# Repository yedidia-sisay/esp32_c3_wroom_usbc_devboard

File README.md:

# ESP32-C3 Custom Development Board

A custom ESP32-C3 development board designed from the ground up in **KiCad**, covering schematic design, component selection, PCB layout, and routing.

The board is built around the **ESP32-C3-WROOM-02** and provides USB-C connectivity, regulated 3.3 V power, programming/debugging interfaces, GPIO expansion, and basic user controls.

## Overview

The goal of this project was to design a practical, compact ESP32-C3 development board rather than relying on an off-the-shelf development board.

The design integrates the ESP32-C3 module with the supporting power, USB, reset, boot, programming, and expansion circuitry required for a usable development platform.

## Features

* **ESP32-C3-WROOM-02** module
* **USB-C** connector
* USB 2.0 D+ / D− connectivity
* USB-C CC resistors
* USB ESD/TVS protection
* **5 V USB input**
* **3.3 V regulated supply**
* AP2112K-3.3 LDO
* Reset / CHIP_PU circuitry
* Boot-mode control
* User/status LED
* GPIO expansion headers
* Dedicated JTAG/UART access
* Exposed 3.3 V, 5 V, and GND connections
* Custom PCB layout and routing

## Hardware

### Main MCU

The board uses the **Espressif ESP32-C3-WROOM-02** module.

The module provides the main processing, USB connectivity, GPIO, UART, and debugging interfaces for the board.

The schematic exposes the ESP32-C3 GPIOs through headers so the board can be used for firmware development and hardware experimentation.

### USB-C

USB-C is used as the primary connection to the board.

The USB interface includes:

* VBUS power input
* USB D+
* USB D−
* CC1 / CC2 configuration resistors
* USB ESD/TVS protection
* Shield connection

The USB data lines connect directly to the ESP32-C3's native USB interface.

### Power

The board accepts **5 V from USB-C**.

A dedicated **AP2112K-3.3 LDO** generates the 3.3 V rail used by the ESP32-C3 and associated circuitry.
Decoupling capacitors are included around the power circuitry and ESP32-C3 supply.

### Reset and Boot

The board includes dedicated push buttons and supporting resistors for:

* ESP32 reset / CHIP_PU
* Boot-mode selection

This allows the module to be manually reset and placed into the required boot mode during firmware development.

### Programming and Debugging

The design exposes the ESP32-C3's programming/debugging signals through dedicated headers.

Interfaces available on the board include:

* UART
* JTAG
* GPIO
* 3.3 V
* 5 V
* GND

### GPIO Expansion

Two multi-pin headers provide access to the ESP32-C3 GPIOs.

This allows external sensors, peripherals, and prototype circuits to be connected without modifying the main PCB.

## PCB Design

The schematic and PCB were designed in **KiCad 10**.

The PCB design process included:

1. Component selection
2. Schematic capture
3. Electrical connectivity definition
4. Component footprint assignment
5. PCB placement
6. Power and signal routing
7. USB routing
8. Ground-plane implementation
9. Design-rule checking
10. Final PCB routing

The design was developed with the intention of producing a physically usable development board rather than being purely a schematic exercise.

# Project Status

**Hardware design completed.**

The schematic and PCB routing have been completed. The next stage is hardware fabrication and bring-up, followed by firmware testing and validation of the USB, power, GPIO, and programming interfaces.
## Author

**Yedidia Sisay**

Electrical Engineering | Embedded Systems | PCB Design

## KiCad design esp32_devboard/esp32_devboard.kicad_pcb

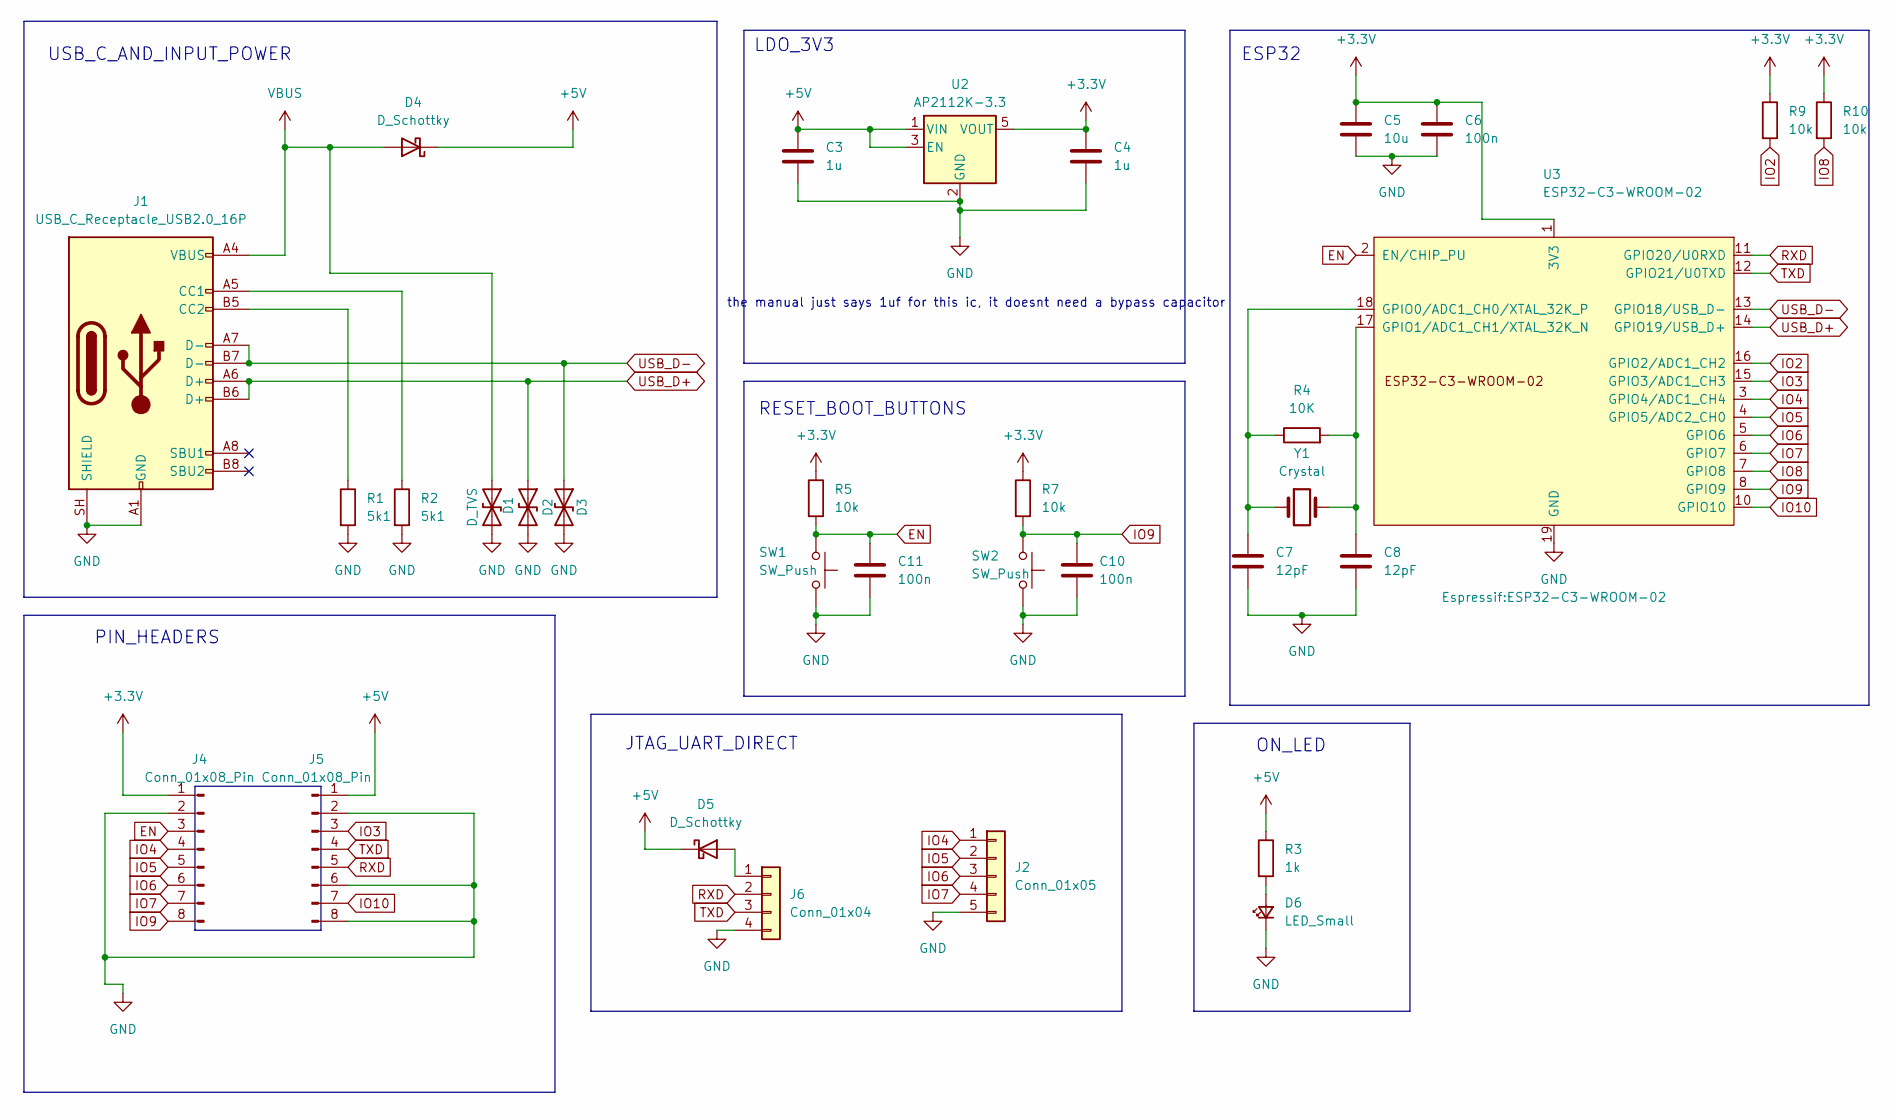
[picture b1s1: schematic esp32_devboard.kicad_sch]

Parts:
C3, C4: 1u; C_0402_1005Metric
C5: 10u; C_0402_1005Metric
C6, C10, C11: 100n; C_0402_1005Metric
C7, C8: 12pF; C_0402_1005Metric
D1, D2, D3: D_TVS; D_SOD-523
D4, D5: D_Schottky; D_SOD-523
D6: LED_Small; LED_0402_1005Metric
J1: USB_C_Receptacle_USB2.0_16P; USB_C_Receptacle_GCT_USB4105-xx-A_16P_TopMnt_Horizontal
J2: Conn_01x05; JST_PH_B5B-PH-K_1x05_P2.00mm_Vertical
J4, J5: Conn_01x08_Pin; PinHeader_1x08_P2.54mm_Vertical
J6: Conn_01x04; JST_PH_B4B-PH-K_1x04_P2.00mm_Vertical
R1, R2: 5k1; R_0402_1005Metric
R3: 1k; R_0402_1005Metric
R4: 10K; R_0402_1005Metric
R5, R7, R9, R10: 10k; R_0402_1005Metric
SW1, SW2: SW_Push; SW_SPST_B3U-1000P
U2: AP2112K-3.3; SOT-23-5
U3: ESP32-C3-WROOM-02
Y1: Crystal; Crystal_SMD_3215-2Pin_3.2x1.5mm

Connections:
+3.3V: C4.1, C5.1, C6.1, J4.1, R5.1, R7.1, R9.1, R10.1, U2.5 (VOUT), U3.1 (3V3)
+5V: C3.1, D4.1 (K), D5.1 (K), J5.1, R3.1, U2.1 (VIN), U2.3 (EN)
EN: C11.1, J4.3, R5.2, SW1.1, U3.2 (EN/CHIP_PU)
GND: C3.2, C4.2, C5.2, C6.2, C7.2, C8.2, C10.2, C11.2, D1.2 (A2), D2.2 (A2), D3.2 (A2), D6.1 (K), J1.A1 (GND), J1.A12 (GND), J1.B1 (GND), J1.B12 (GND), J1.SH (SHIELD), J2.5, J4.2, J5.2, J5.6, J5.8, J6.4, R1.2, R2.2, SW1.2, SW2.2, U2.2 (GND), U3.9 (GND), U3.19 (GND)
IO2: R9.2, U3.16 (GPIO2/ADC1_CH2)
IO3: J5.3, U3.15 (GPIO3/ADC1_CH3)
IO4: J2.1, J4.4, U3.3 (GPIO4/ADC1_CH4)
IO5: J2.2, J4.5, U3.4 (GPIO5/ADC2_CH0)
IO6: J2.3, J4.6, U3.5 (GPIO6)
IO7: J2.4, J4.7, U3.6 (GPIO7)
IO8: R10.2, U3.7 (GPIO8)
IO9: C10.1, J4.8, R7.2, SW2.1, U3.8 (GPIO9)
IO10: J5.7, U3.10 (GPIO10)
unnamed: D5.2 (A), J6.1
unnamed: D6.2 (A), R3.2
unnamed: J1.A5 (CC1), R2.1
unnamed: J1.B5 (CC2), R1.1
unnamed: C7.1, R4.1, U3.18 (GPIO0/ADC1_CH0/XTAL_32K_P), Y1.1
unnamed: C8.1, R4.2, U3.17 (GPIO1/ADC1_CH1/XTAL_32K_N), Y1.2
RXD: J5.5, J6.2, U3.11 (GPIO20/U0RXD)
TXD: J5.4, J6.3, U3.12 (GPIO21/U0TXD)
USB_D+: D2.1 (A1), J1.A6 (D+), J1.B6 (D+), U3.14 (GPIO19/USB_D+)
USB_D-: D3.1 (A1), J1.A7 (D-), J1.B7 (D-), U3.13 (GPIO18/USB_D-)
VBUS: D1.1 (A1), D4.2 (A), J1.A4 (VBUS), J1.A9 (VBUS), J1.B4 (VBUS), J1.B9 (VBUS)

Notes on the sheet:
the manual just says 1uf for this ic, it doesnt need a bypass capacitor
ESP32
USB_C_AND_INPUT_POWER
ON_LED
PIN_HEADERS
JTAG_UART_DIRECT
LDO_3V3
RESET_BOOT_BUTTONS

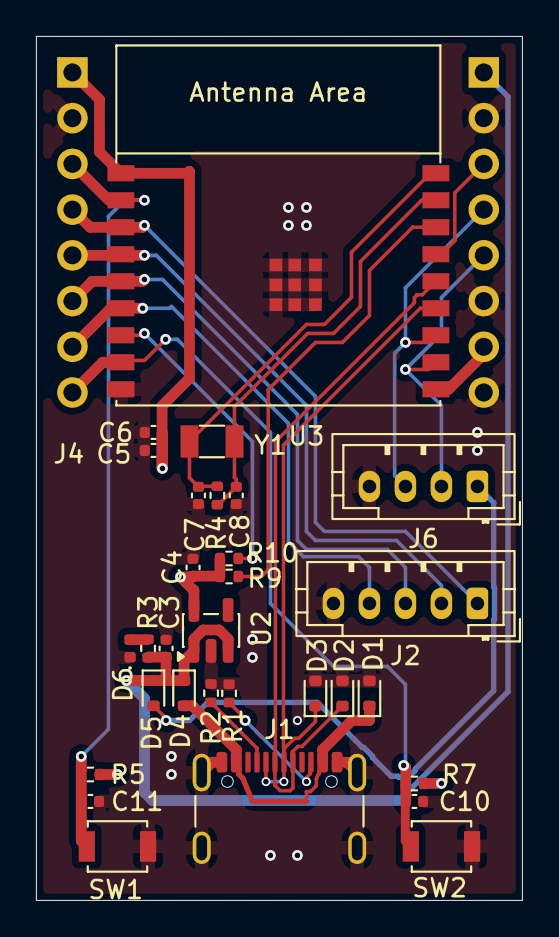
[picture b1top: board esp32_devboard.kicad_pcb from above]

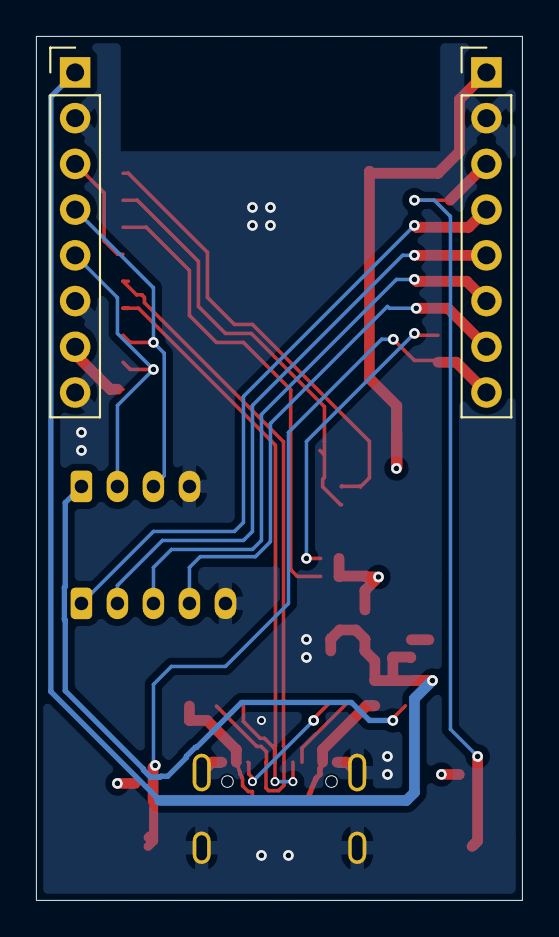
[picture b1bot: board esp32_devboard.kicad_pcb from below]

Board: 4 copper layers, 27.0 x 48.0 mm, 32 parts (2 on the bottom side), 24 nets.

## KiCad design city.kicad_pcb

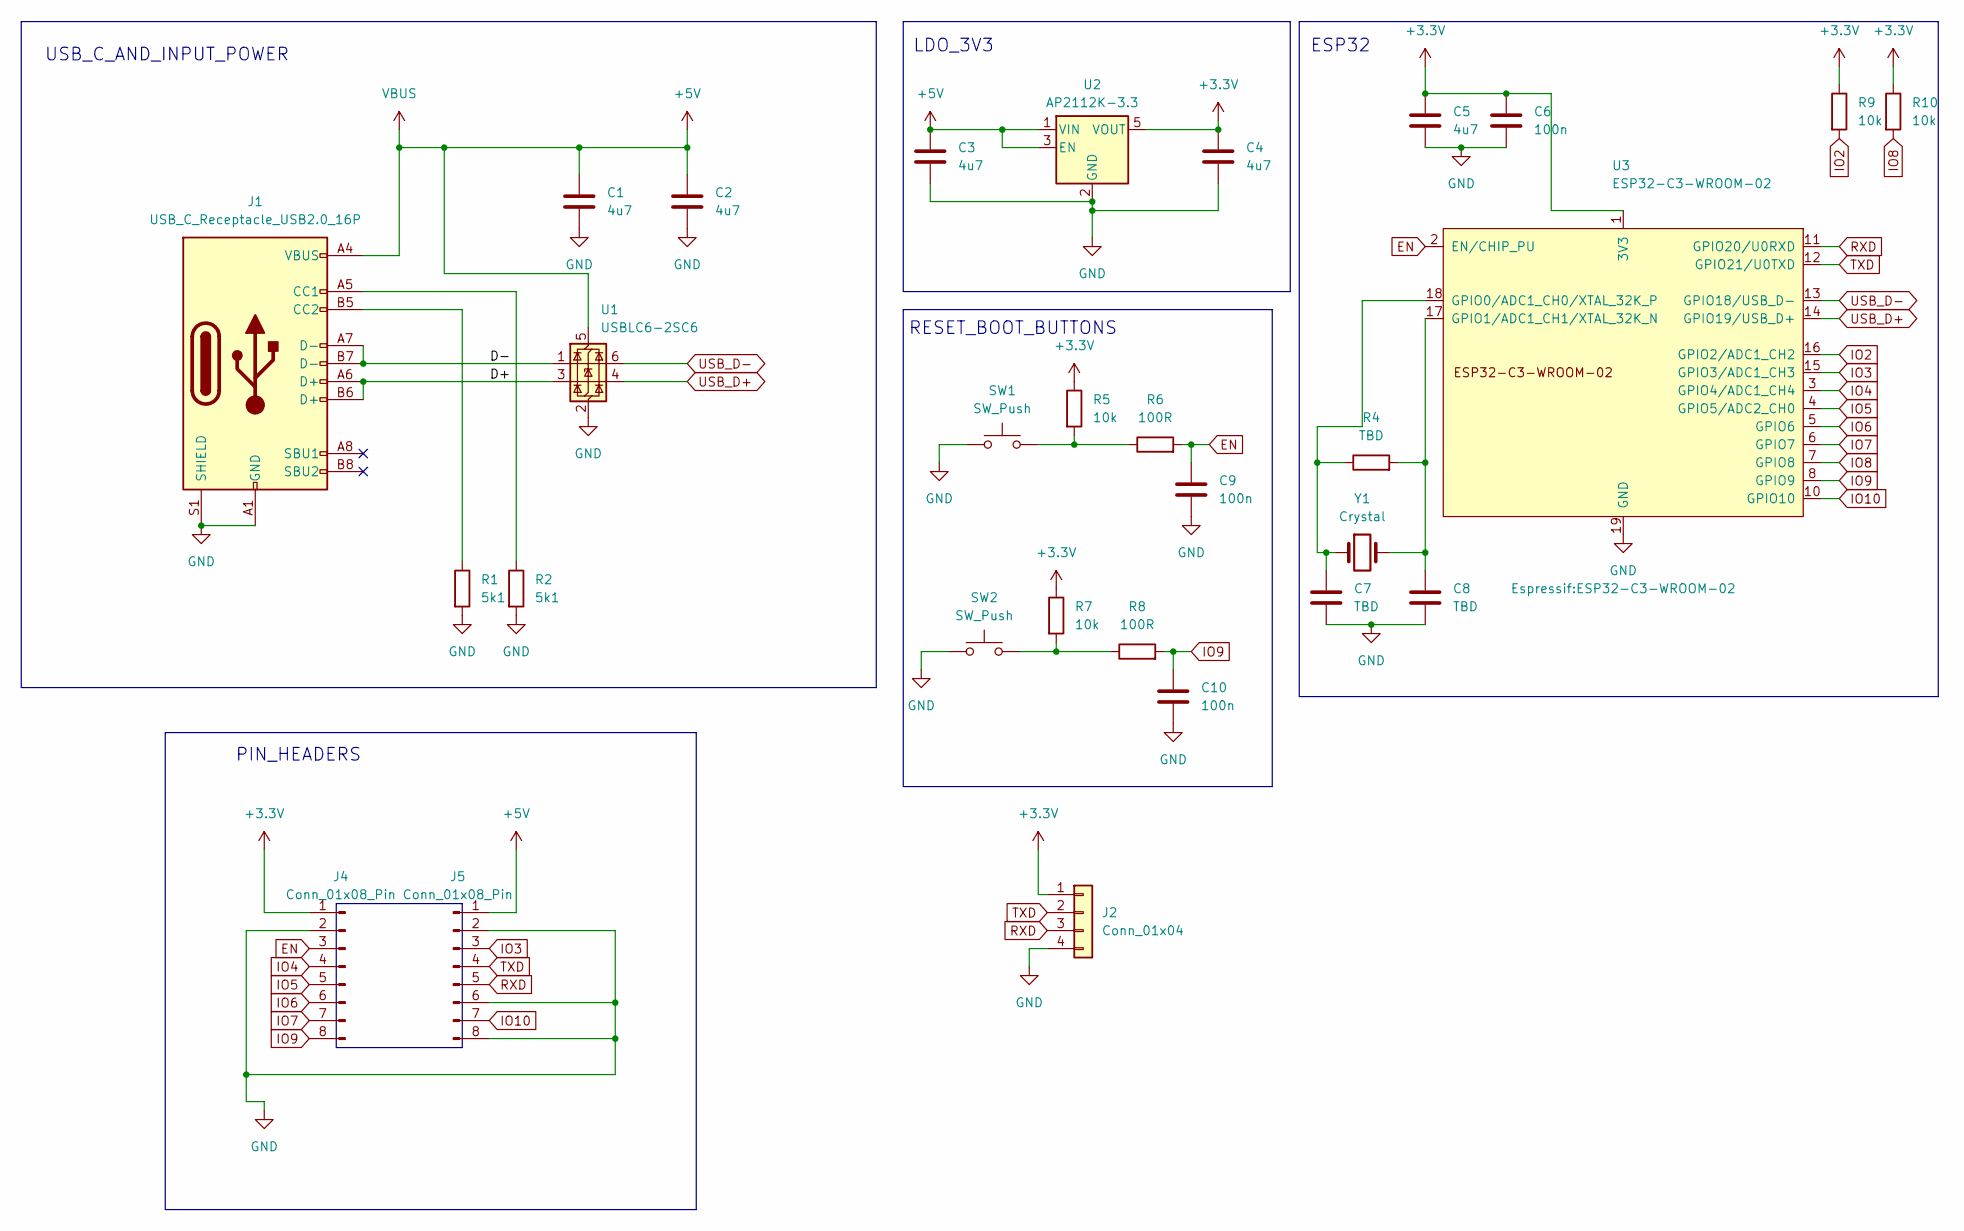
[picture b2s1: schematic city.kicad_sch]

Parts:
C1, C2, C3, C4, C5: 4u7; C_0805_2012Metric
C6, C9, C10: 100n; C_0402_1005Metric
C7, C8: TBD; C_0402_1005Metric
J1: USB_C_Receptacle_USB2.0_16P; USB_C_Receptacle_G-Switch_GT-USB-7010ASV
J2: Conn_01x04; PinHeader_1x04_P2.00mm_Vertical
J4, J5: Conn_01x08_Pin; PinHeader_1x08_P2.54mm_Vertical
R1, R2: 5k1; R_0402_1005Metric
R4: TBD; R_0402_1005Metric
R5, R7, R9, R10: 10k; R_0402_1005Metric
R6, R8: 100R; R_0402_1005Metric
SW1, SW2: SW_Push; SW_SPST_B3U-1000P
U1: USBLC6-2SC6; SOT-23-6
U2: AP2112K-3.3; SOT-23-5
U3: ESP32-C3-WROOM-02
Y1: Crystal; Crystal_SMD_3215-2Pin_3.2x1.5mm

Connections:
+3.3V: C4.1, C5.1, C6.1, J2.1, J4.1, R5.1, R7.1, R9.1, R10.1, U2.5 (VOUT), U3.1 (3V3)
+5V: C1.1, C2.1, C3.1, J1.A4 (VBUS), J1.A9 (VBUS), J1.B4 (VBUS), J1.B9 (VBUS), J5.1, U1.5 (VBUS), U2.1 (VIN), U2.3 (EN)
/D+: J1.A6 (D+), J1.B6 (D+), U1.3 (I/O2)
/D-: J1.A7 (D-), J1.B7 (D-), U1.1 (I/O1)
EN: C9.1, J4.3, R6.2, U3.2 (EN/CHIP_PU)
GND: C1.2, C2.2, C3.2, C4.2, C5.2, C6.2, C7.2, C8.2, C9.2, C10.2, J1.A1 (GND), J1.A12 (GND), J1.B1 (GND), J1.B12 (GND), J1.S1 (SHIELD), J2.4, J4.2, J5.2, J5.6, J5.8, R1.2, R2.2, SW1.1, SW2.1, U1.2 (GND), U2.2 (GND), U3.9 (GND), U3.19 (GND)
IO2: R9.2, U3.16 (GPIO2/ADC1_CH2)
IO3: J5.3, U3.15 (GPIO3/ADC1_CH3)
IO4: J4.4, U3.3 (GPIO4/ADC1_CH4)
IO5: J4.5, U3.4 (GPIO5/ADC2_CH0)
IO6: J4.6, U3.5 (GPIO6)
IO7: J4.7, U3.6 (GPIO7)
IO8: R10.2, U3.7 (GPIO8)
IO9: C10.1, J4.8, R8.2, U3.8 (GPIO9)
IO10: J5.7, U3.10 (GPIO10)
unnamed: J1.A5 (CC1), R2.1
unnamed: J1.B5 (CC2), R1.1
unnamed: R5.2, R6.1, SW1.2
unnamed: R7.2, R8.1, SW2.2
unnamed: C7.1, R4.1, U3.18 (GPIO0/ADC1_CH0/XTAL_32K_P), Y1.1
unnamed: C8.1, R4.2, U3.17 (GPIO1/ADC1_CH1/XTAL_32K_N), Y1.2
RXD: J2.3, J5.5, U3.11 (GPIO20/U0RXD)
TXD: J2.2, J5.4, U3.12 (GPIO21/U0TXD)
USB_D+: U1.4 (I/O2), U3.14 (GPIO19/USB_D+)
USB_D-: U1.6 (I/O1), U3.13 (GPIO18/USB_D-)

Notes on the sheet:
LDO_3V3
ESP32
RESET_BOOT_BUTTONS
USB_C_AND_INPUT_POWER
PIN_HEADERS

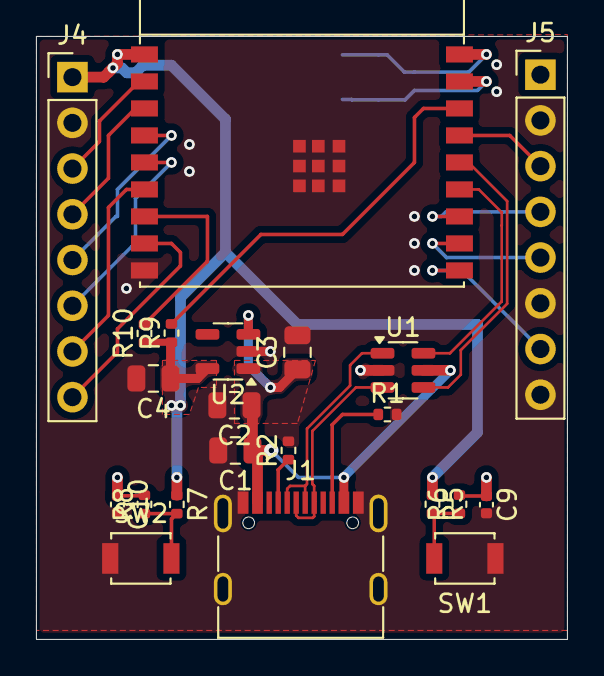
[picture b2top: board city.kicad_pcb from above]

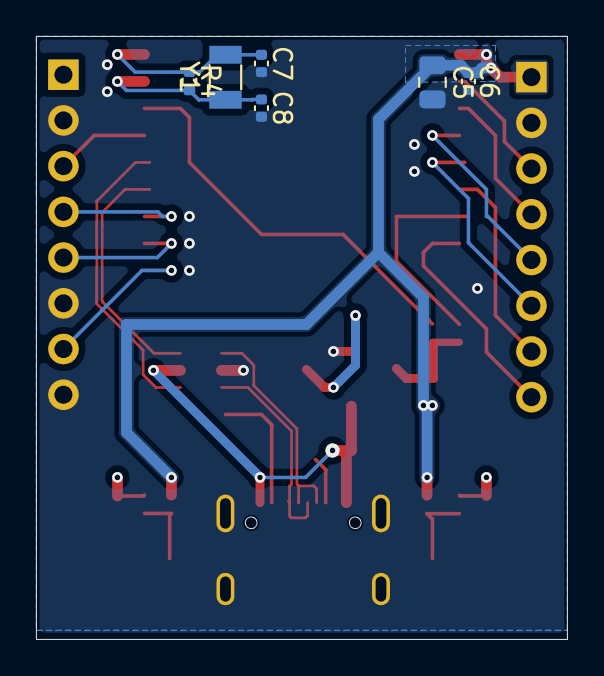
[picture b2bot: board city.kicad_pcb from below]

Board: 4 copper layers, 29.5 x 33.5 mm, 28 parts (6 on the bottom side), 25 nets.
